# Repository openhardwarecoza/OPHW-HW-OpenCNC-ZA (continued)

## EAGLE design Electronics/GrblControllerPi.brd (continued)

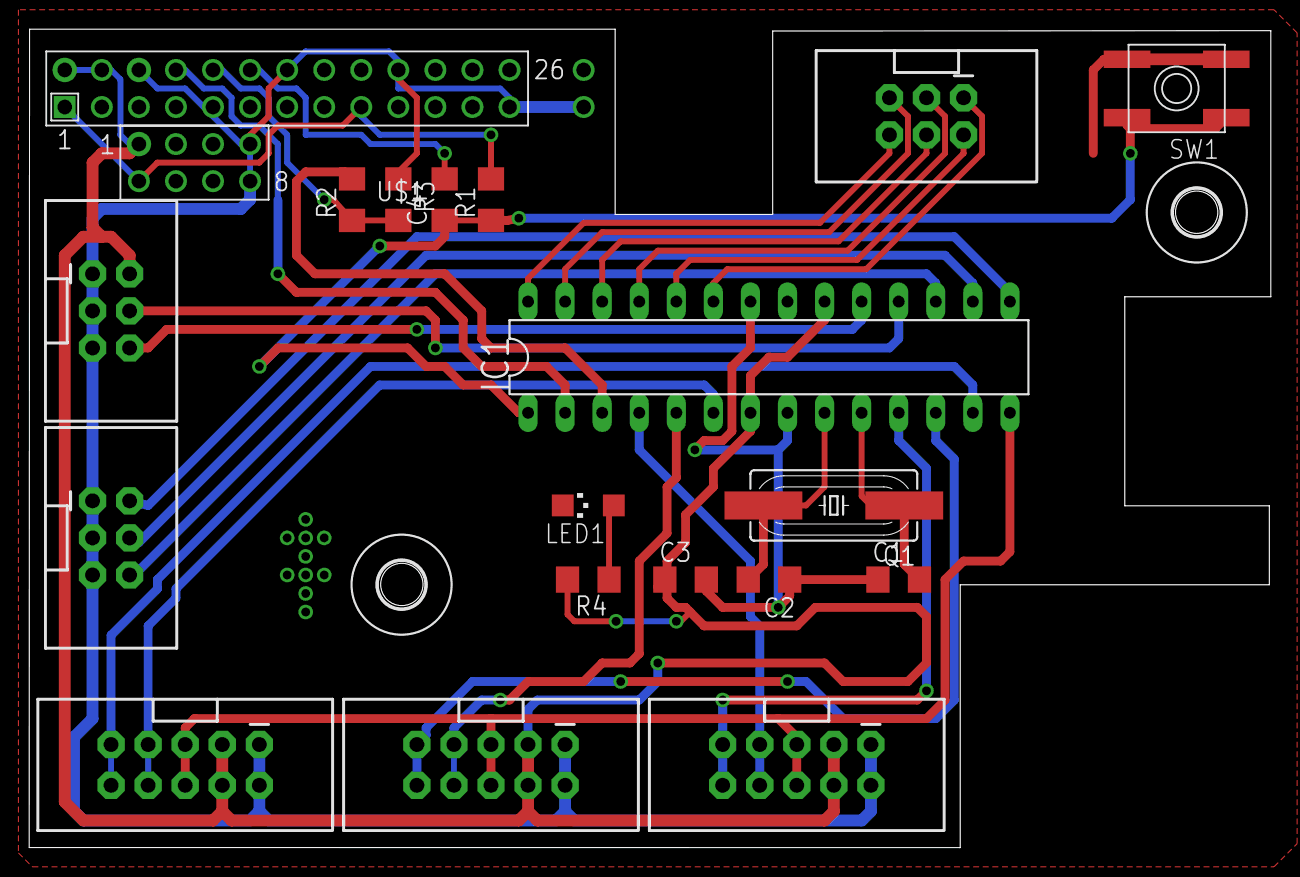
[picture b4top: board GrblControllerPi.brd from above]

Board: 2 copper layers, 85.1 x 56.1 mm, 21 parts (0 on the bottom side), 29 nets.

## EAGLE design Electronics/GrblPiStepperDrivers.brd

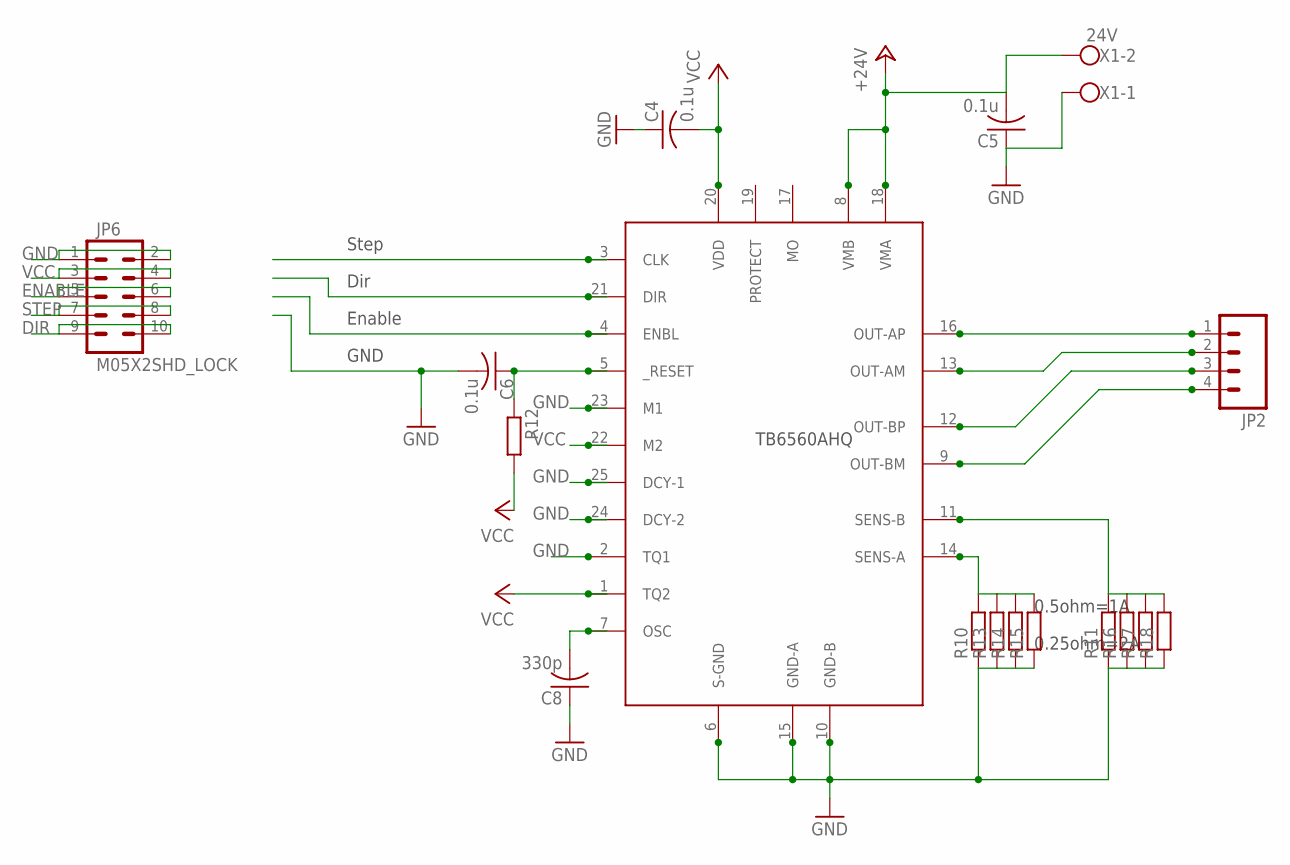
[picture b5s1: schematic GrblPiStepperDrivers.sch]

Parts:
C4, C5, C6: 0.1u; C1206K
C8: 330p; C1206K
JP2: M04SCREW; SCREWTERMINAL-3.5MM-4
JP6: M05X2SHD_LOCK; 2X5-SHROUDED_LOCK
R10, R11, R13, R14, R15, R16, R17, R18: R-EU_0411/3V; 0411V
R12: R-EU_M1206; M1206
U$2: TB6560-H; ZIP25-H
X1: 24V; W237-102

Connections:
+24V: C5.2, U$2.8 (VMB), U$2.18 (VMA), X1.2
DIR: JP6.9, JP6.10, U$2.21 (DIR)
ENABLE: JP6.5, JP6.6, U$2.4 (ENBL)
GND: C4.1, C5.1, C6.2, C8.1, JP6.1, JP6.2, R10.1, R11.1, R13.1, R14.1, R15.1, R16.1, R17.1, R18.1, U$2.2 (TQ1), U$2.6 (S-GND), U$2.10 (GND-B), U$2.15 (GND-A), U$2.23 (M1), U$2.24 (DCY-2), U$2.25 (DCY-1), X1.1
unnamed: R10.2, R13.2, R14.2, R15.2, U$2.14 (SENS-A)
unnamed: R11.2, R16.2, R17.2, R18.2, U$2.11 (SENS-B)
unnamed: JP2.1, U$2.16 (OUT-AP)
unnamed: C8.2, U$2.7 (OSC)
unnamed: C6.1, R12.1, U$2.5 (_RESET)
unnamed: JP2.3, U$2.12 (OUT-BP)
unnamed: JP2.2, U$2.13 (OUT-AM)
unnamed: JP2.4, U$2.9 (OUT-BM)
STEP: JP6.7, JP6.8, U$2.3 (CLK)
VCC: C4.2, JP6.3, JP6.4, R12.2, U$2.1 (TQ2), U$2.20 (VDD), U$2.22 (M2)

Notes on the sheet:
Step
Dir
Enable
GND
0.5ohm=1A
0.25ohm=2A
TB6560AHQ

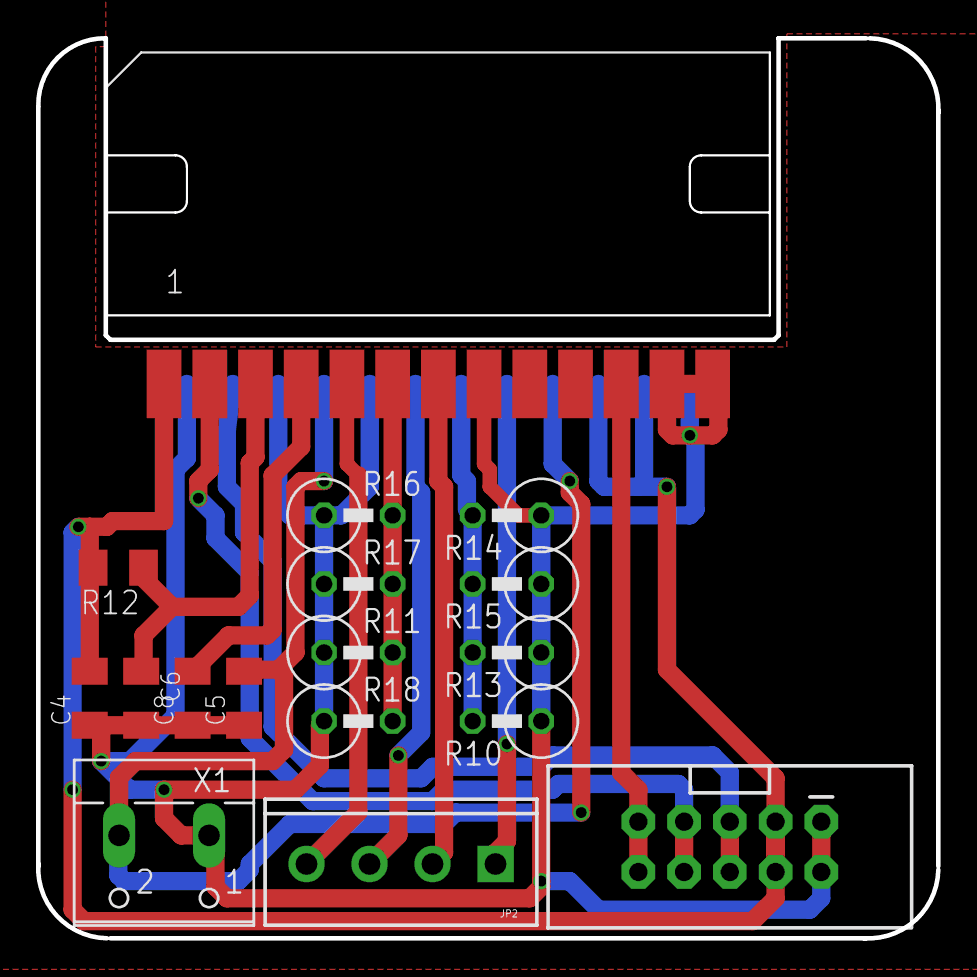
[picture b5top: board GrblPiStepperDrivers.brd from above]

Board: 2 copper layers, 50.0 x 50.0 mm, 17 parts (0 on the bottom side), 14 nets.

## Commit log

2014-06-16 First commit of Mechanical and Electronic
2014-07-03 Changed the dimensions of some parts after beta
    Fixed some spacing issues we had during BETA1
2014-07-15 Added Stepper Driver
2014-07-28 Minor Tweaks to hardware + Added GrblpiB+ boards
2014-08-15 Added GrblPi Industrial
2014-08-15 Industrial Version: Gerbers as ordered
2015-05-28 Single sided for Nicholas
2016-01-26 Added Photos
2016-01-26 Cleaned up
2016-01-26 Added Readme
2016-01-26 Added Ballscrew Instructions
2016-01-26 Added BOM
2016-01-26 Deleted Temp File
2016-02-02 OpenCNC-SMW3D
2016-02-02 OpenCNC-SMW3D - removed temp files
2016-02-03 Torsion Clamp Plate, fixed X idler mount, removed C-Beam Z Axis
2016-02-10 OpenCNC-SMW3d work...
2016-02-20 DXF for Samer
2016-05-08 BOM, Ballscrew sketch, and update drawing of CNC with spacers
2018-05-01 Reupload
